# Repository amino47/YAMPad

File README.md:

# YAMPad
YAMPad is a 6 key macropad running on KMK firmware with a Seeed Studio XIAO RP2040 as the MCU. 
It's default keymap includes layer switching, media key support and a mouse jiggler.

# My Struggles
One of my major struggles when designing this project was making the case, as I am very new to CAD. 
I mainly struggled with aligning the measurements and cutouts between the top and bottom sections of the case. 
I probably spent at least 40% of the time making this project on just designing the case. 
I eventually managed to align the cutout for the MCU on both pieces of the case.

## BOM
1x Seeed Studio XIAO RP2040 <br>
1x PCB <br>
1x 3D Printed case <br>
6x Cherry MX compatible switches. <br>
6x keycaps <br>
4x M3 Screws <br>

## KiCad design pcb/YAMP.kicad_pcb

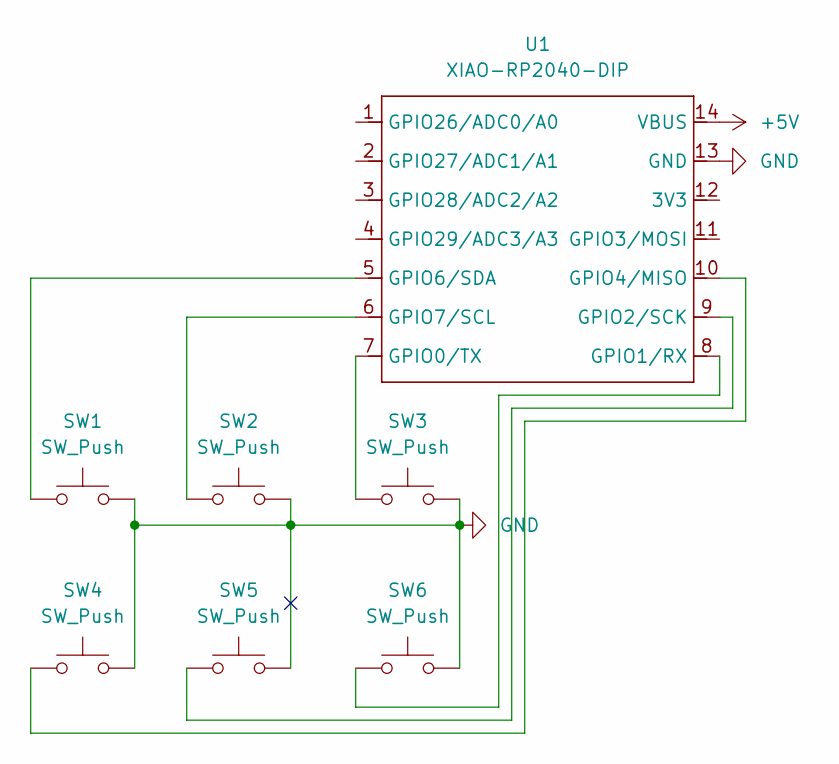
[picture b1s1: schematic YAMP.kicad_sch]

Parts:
SW1, SW2, SW3, SW4, SW5, SW6: SW_Push; SW_Cherry_MX_1.00u_PCB
U1: XIAO-RP2040-DIP

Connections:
+5V: U1.14 (VBUS)
GND: SW1.2, SW2.2, SW3.2, SW4.2, SW5.2, SW6.2, U1.13 (GND)
unnamed: SW3.1, U1.7 (GPIO0/TX)
unnamed: SW6.1, U1.8 (GPIO1/RX)
unnamed: SW5.1, U1.9 (GPIO2/SCK)
unnamed: SW4.1, U1.10 (GPIO4/MISO)
unnamed: SW1.1, U1.5 (GPIO6/SDA)
unnamed: SW2.1, U1.6 (GPIO7/SCL)

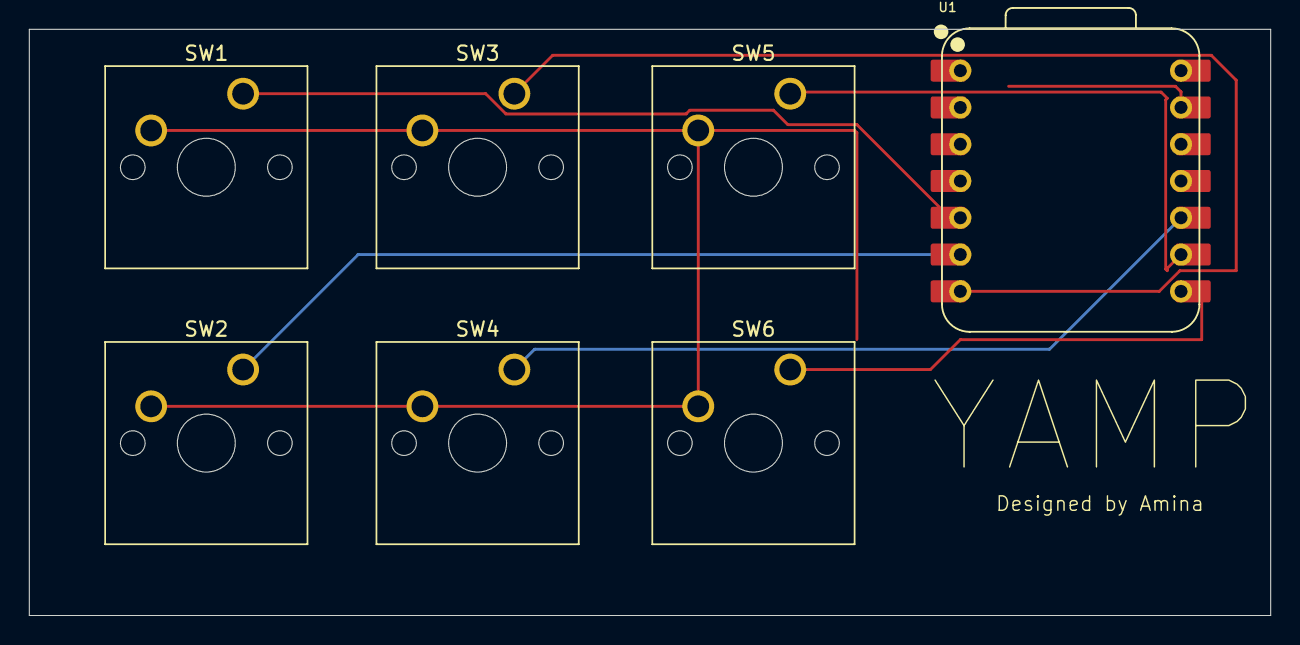
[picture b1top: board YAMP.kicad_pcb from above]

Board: 2 copper layers, 85.7 x 40.5 mm, 7 parts (0 on the bottom side), 7 nets.

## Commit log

2025-06-11 add kicad files to repo
2025-06-11 add branding to PCB
2025-06-13 add existing files
2025-06-13 add README. plus reorganize files
2025-06-13 fix images in readme
2025-06-13 fix BOM newlines in README.md
2025-06-13 add way to get to layer 2 in firmware
2025-06-13 remove unused encoder from schematic file
2025-06-14 add struggles to the readme
2025-06-14 add more features to the readme
